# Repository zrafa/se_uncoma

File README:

Proyecto de Hardware y Software para el estudio de los Sistemas Embebidos
-------------------------------------------------------------------------

Este repositorio contiene principalmente toda la documentación y código fuente
del hardware y software del robot educativo "Frankestito", construido en la
Facultad de Informática, Universidad Nacional del Comahue

* Written 2011-2013 by Rafael Ignacio Zurita y Rodolfo del Castillo
* Copyright 2011-2013 by Rafael Ignacio Zurita y Rodolfo del Castillo

Todo el software escrito el hardware desarrollado para el robot (ya sean scripts, biblioteca de visión,
programa para sincronización, modificaciones de Myro en python y C, programas de
ejemplo, firmware del ATMEGA8, esquematicos, diseños de circuitos) y todo archivo fuente de este proyecto es Software Libre y Hardware Copyleft.

Encontrará una copia de la Licencia en el archivo COPYING.GPL o LICENSE, el cual contiene
las condiciones bajo las cuales puede utilizar, modificar, y/o redistribuir el software y
hardware.

This package is free software; you can redistribute it and/or modify
it under the terms of the GNU General Public License as published by
the Free Software Foundation; either version 2 of the License, or
(at your option) any later version.

See the file COPYING.GPL for details.

Los archivos restantes que sean componentes reutilizados tienen su propia licencia
de hardware o software. Debe verificar esas licencias antes de decidir si puede
reutilizar, modificar, o distribuir esos componentes.

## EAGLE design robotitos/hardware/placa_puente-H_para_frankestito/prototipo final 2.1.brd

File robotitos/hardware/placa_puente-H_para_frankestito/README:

Shield for EasyDuino. This board controls two motors, leds, buzzer and implements the Myro protocol

Schematis and design of the circuit

This hardware is part of the Frankestito robot for education project

Copyright Jose Riquelme <jose.riquelme@fi.uncoma.edu.ar>
Licensed under CC-BY-SA 3.0

You are free to:

Share — copy and redistribute the material in any medium or format
Adapt — remix, transform, and build upon the material
for any purpose, even commercially.
The licensor cannot revoke these freedoms as long as you follow the license terms.

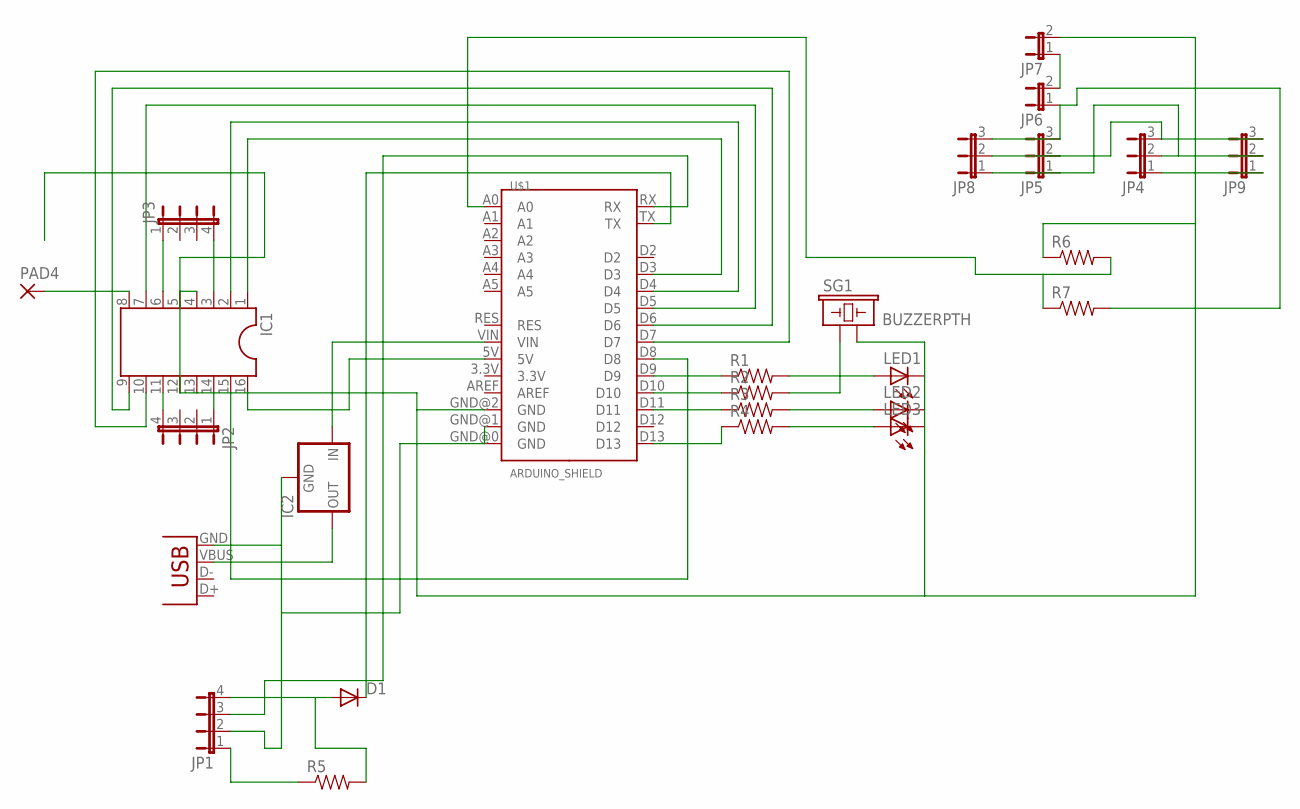
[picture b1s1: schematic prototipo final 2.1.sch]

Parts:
D1: DIODEPTH; DIODE-1N4001
IC1: DIL16S; SOCKET-16
IC2: V_REG_78XXSINK; TO220-IGO
JP1, JP2, JP3: JP4E; JP4
JP4, JP5, JP8, JP9: JP2E; JP2
JP6, JP7: JP1E; JP1
LED1, LED2, LED3: LED3MM
PAD4: 2,15/1,0
R1, R2, R3, R4, R5, R6, R7: RESISTORPTH1; AXIAL-0.3
SG1: BUZZERPTH; BUZZER-12MM
U$1: ARDUINO_SHIELD; DUEMILANOVE_SHIELD
X1: USB-A-S

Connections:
unnamed: IC1.1, U$1.D3
unnamed: IC1.2, U$1.D4
unnamed: IC1.6, JP3.1
unnamed: IC1.3, JP3.4
unnamed: IC1.11, JP2.4
unnamed: IC1.14, JP2.1
unnamed: IC1.16, U$1.5V
unnamed: JP5.3, JP6.1, JP8.3, R7.P$2 (2)
unnamed: IC2.OUT, X1.VBUS
unnamed: IC1.8, PAD4.1
unnamed: IC1.7, U$1.D5
unnamed: R4.P$1 (1), U$1.D13
unnamed: IC1.9, U$1.D6
unnamed: IC1.10, U$1.D7
unnamed: IC2.GND, JP1.2, U$1.GND@0 (GND), U$1.GND@1 (GND), X1.GND
unnamed: IC1.15, U$1.D8
unnamed: R1.P$1 (1), U$1.D9
unnamed: R2.P$1 (1), U$1.D10
unnamed: R3.P$1 (1), U$1.D11
unnamed: IC1.4, IC1.5, IC1.12, IC1.13, JP4.1, JP7.2, JP9.1, LED1.K (C), LED2.K (C), LED3.K (C), R6.P$1 (1), SG1.- (2), U$1.GND@2 (GND)
unnamed: LED3.A, R4.P$2 (2)
unnamed: LED2.A, R3.P$2 (2)
unnamed: LED1.A, R1.P$2 (2)
unnamed: JP4.2, JP5.1, JP8.1, JP9.2
unnamed: JP1.1, R5.P$1 (1)
unnamed: JP4.3, JP5.2, JP8.2, JP9.3
unnamed: R2.P$2 (2), SG1.+ (1)
unnamed: JP6.2, JP7.1
unnamed: R6.P$2 (2), R7.P$1 (1), U$1.A0
unnamed: D1.C, U$1.TX
unnamed: D1.A, JP1.4, R5.P$2 (2)
unnamed: JP1.3, U$1.RX
unnamed: IC2.IN, U$1.VIN

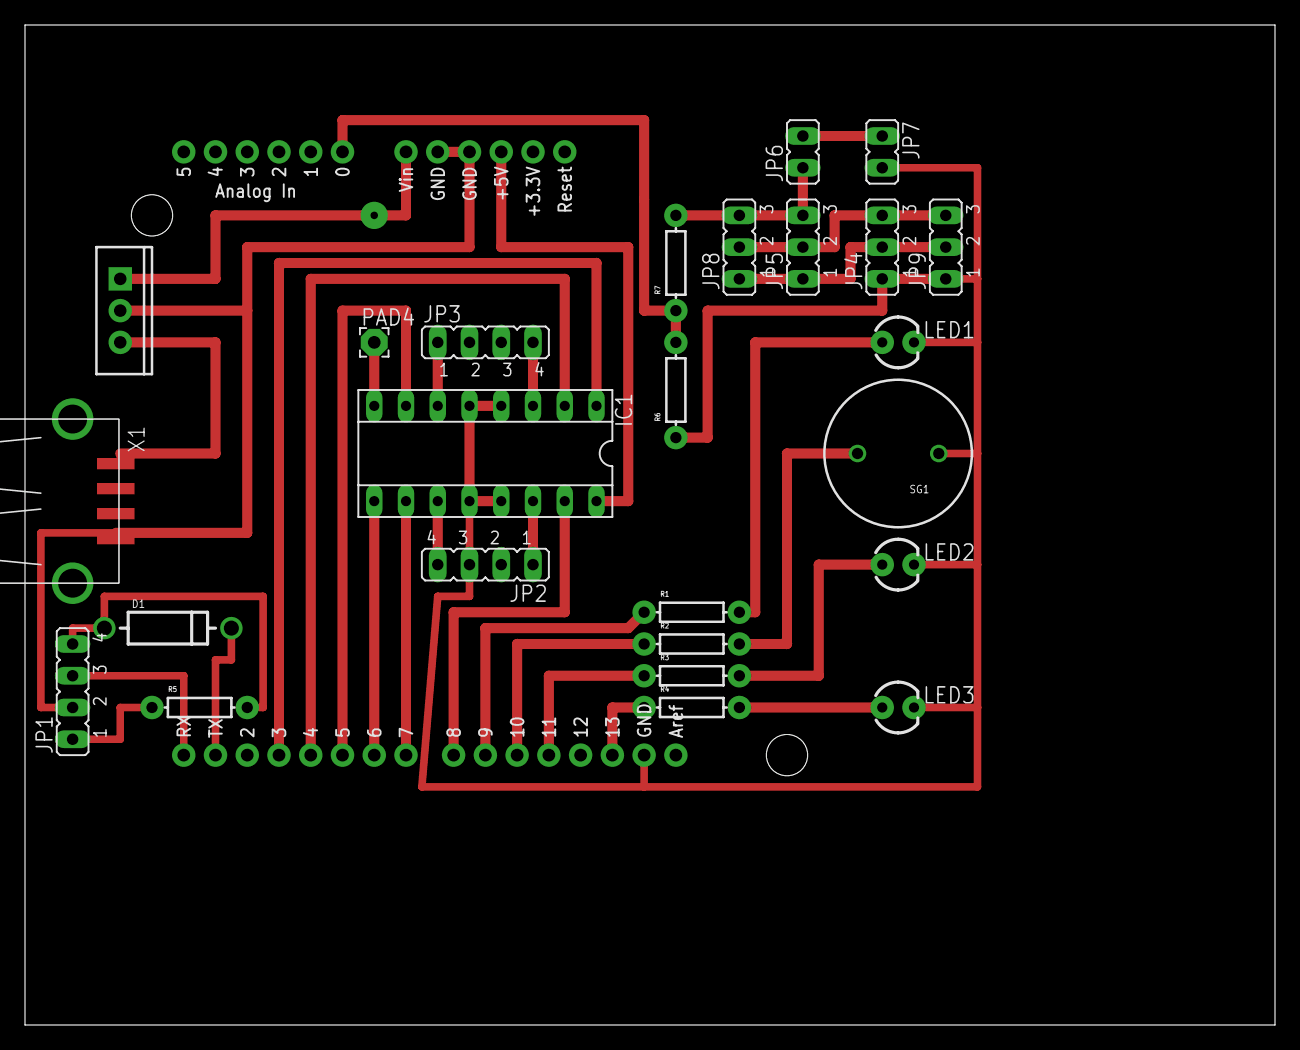
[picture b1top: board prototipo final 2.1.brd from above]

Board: 2 copper layers, 100.0 x 80.0 mm, 26 parts (0 on the bottom side), 33 nets.

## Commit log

2013-03-13 Agregamos los documentos que justifican el proyecto
2013-03-13 Colocamos los documentos en docs
2013-03-20 Agrego el comando que sincroniza la PC con el robot
2013-03-20 Agrego el README al sync
2013-03-20 Agregamos el codigo fuente del arduino para controlar el robot
2013-03-20 Agregamos la version de myro en C con ejemplos
2013-03-20 movemos la version de myro de c
2013-03-20 Agregamos la libreria de vision
2013-03-20 agregamos las instrucciones de python
2013-03-20 Agregamos ejemplos en python
2013-03-20 Agregamos el codigo fuente de myro
2013-03-20 Mejoras del oso para hacerlo mas facil
2013-03-20 Quitamos los mensajes de logs
2013-03-21 buscamos la velocidad inicial minima
2013-03-21 Ejemplo testeado
2013-03-21 cambiamos la ip
2013-03-22 anulamos los printf molestos
2013-03-22 Comenzamos con el proceso de modificacion a N robots
2013-03-22 mejora del oso funcionando con robot 2013
2013-03-22 mejoras sustanciales
2013-03-22 mejoras sustanciales 2
2013-03-27 ejemplos y tests
2013-03-27 Mejoramos el ejemplo de sincronizacion
2013-03-27 Algunos tests
2013-03-27 Agregamos la mejora de que duino_sync este en el PATH
2013-03-30 agregamos una espera al socat
2013-03-30 solucionamos un problema tonto con argv
2013-04-01 varios cambios : convert screen image
2013-04-01 agregamos la diferencia de lenguajes
2013-04-03 Otra vez tuvimos problemas con las bibliotecas
2013-04-03 minima mejora para que funcione con el robot actual
2013-04-04 Agrego algunos metodos usados mas
2013-04-04 Agrego un nombre nuevo a robo2
2013-04-05 agregamos el instalador automatico
2013-04-05 instrucciones de instalacion automatizada
2013-05-30 README
2013-06-25 generalizamos la ip del robot en la biblioteca de vision
2013-07-28 dia 1
2013-07-28 curso arduino
2013-07-28 easyduino
2013-07-28 plan
2013-07-29 documentacion
2013-07-29 mejoras a la planificacion del taller
2013-07-29 atmega8 hoja de datos
2013-07-29 mas documentos iniciales
2013-08-02 mejoramos la vision ¨
2013-08-02 modificamos dos archivos
2013-08-23 movemos el hardware
2013-08-27 puente H
2013-09-11 licencia faltante
2013-09-11 agregamos informacion de distribucion
2013-09-14 calibracion
2013-09-14 calibrar
2013-09-14 ejemplos
2013-09-14 agregamos la licencia que eliminamos anteriormente
2013-09-14 quitamos los binarios
2013-09-19 pagina web
2013-10-01 comunicaciones
2013-10-01 cambiamos el nombre
2013-12-11 agregamos la documentacion linux
2014-01-02 Codigo fuente en eagle de la plaquita puente H
2014-03-27 comentarios
2014-05-05 myro-cpp
2014-05-05 rmbuild
2014-05-07 fpic
2014-05-11 Agregamos mejora al sync
2014-05-11 mejoramos los problemas y soluciones
2014-05-12 proxima version utilizando opencv
2014-05-21 codigo para manejar motores con nueva placa l293d
2014-06-11 nueva version que ve colores de verdad
2014-06-11 primera version con cvblob
2014-06-11 mas mejoras
2014-06-11 un ejemplo del robot buscando la pelota
2014-06-11 makefile
2014-06-17 limpieza decente
2014-06-17 primera version para los registros
2014-06-22 configuracion serial
2014-06-24 fix del nombre
2014-06-24 mejoramos el estado de la conexion
2014-07-29 agregamos paquete que falta
2014-07-29 mejoramos la instalacion
2014-07-29 agregamos el 3er robot
2014-07-29 binarios
2014-07-29 binario correcto
2014-07-29 robofai2
2014-08-01 cvblob
2014-08-11 licencias de hw
2014-08-12 detalles
2015-05-12 documentacion del linux del mr3020
2015-05-12 conexion serial
2015-05-12 repositorio
2015-05-12 passwd
2015-05-13 mejoras
2015-05-14 correcciones
2015-06-01 robofai3 version nueva
2015-06-24 Mejoramos el script para fidebian
2015-06-24 Mejoramos el script para fidebian 2
2015-06-24 Mejoramos el script para fidebian 3
2015-06-24 binario para flashear nuevos robots
2015-09-04 listado de componentes
2015-09-04 ubicacion de componentes
2016-05-13 instrucciones para programar un duinobot
2016-05-13 ejemplo motores
2016-05-17 Nuevo robot N6 integrado a faiduino
2016-05-17 Actualizacion de la documentacion
2016-05-24 unsigned NO mejor signed
2016-06-30 version para N6
2016-07-01 documentacion de la instalacion de openwrt sobre mr3040
2016-07-05 cambios menores
2016-07-05 correccion de ssh
2016-07-05 correcciones menores
2016-07-06 la velocidad no es la correcta
2016-08-18 serial correcto
2016-08-25 utilizar el robot de manera basica desde python
2016-09-22 Direccion correcta
2017-09-06 Committer: Juan M. de la Fuente <jmdelafuente22@gmail.com>
2017-09-09 Correccion de errores: añadido los paquetes de video y actualizado el script para iniciar la camara
2017-09-09 Corregida la conexion telnet/ssh y añadidos comentarios
2017-09-14 Cargadas las instrucciones para flashear mr3020 en el proyecto de fabricacion de robots para media
2017-10-13 para cosas viejas
2018-03-14 Actualizadas las instrucciones de instalación de Myro
2018-03-14 markdown actualizado en el readme
2018-03-14 Delete README
    Actualizado para soportar markdown
2026-03-19 prueba para usar motores sin myro
